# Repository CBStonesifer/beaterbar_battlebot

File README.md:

# Beater-Bar BattleBot

A 3-pound (beetleweight) combat robot designed and built across the full hardware stack: mechanical CAD, PCB layout, and embedded firmware. The goal was a **reproducible end-to-end build process** — from CAD model to fabricated board to driving firmware — rather than peak performance. V2 will optimize for weight and combat performance.

> A full reflection on the build is on Substack: [Earning Three Minutes in the Ring](https://open.substack.com/pub/carterstonesifer/p/earning-three-minutes-in-the-ring?r=2y2f28&utm_campaign=post&utm_medium=web&showWelcomeOnShare=true)

**Skills demonstrated:** Fusion 360 / FDM prototyping · KiCad schematic + layout · custom footprint creation · Gerber fabrication output · ESP32 embedded C · RC PWM decode · LEDC motor PWM · skid-steer mixing

---

## Repo Structure

```
cad/          — 3D-printable chassis, wheels, and weapon (STL + 3MF)
pcb/          — KiCad schematic, layout, custom footprints, and gerbers
firmware/     — Arduino sketch for ESP32 (RC decode + motor mixing)
```

---

## Design Decisions

- **Beater bar weapon** — a relatively simple and proven design with high impact potential in the arena. The main weakness is being flipped; a lower profile in V2 addresses this directly.
- **Unified motor driver (DRV8833)** — the same driver module is used for all three motors (left drive, right drive, weapon). Simplifies the BOM and firmware; the weapon motor runs off its own dedicated DRV8833 instance.
- **Skid-steer drivetrain** — keeps mechanical complexity low while maintaining full mobility. No steering linkage, no Ackermann geometry, just two independently driven wheels.
- **Belt-driven weapon** — the GT2 20T/60T pulley ratio amplifies the motor's output speed to spin the beater bar faster than a direct-drive setup would allow.
- **Unitary printed body** — a single-piece chassis provides structural strength without mechanical interlocks between parts. Drive and weapon geometry were validated as separate prints first, then merged once the layout was confirmed.

---

## Bill of Materials

| # | Component | Part | Qty | Specs | Link |
|---|-----------|------|-----|-------|------|
| 1 | MCU | ESP32 dev board | 1 | Dual-core 32-bit, 240 MHz, 3.3V, WiFi + BT | [Amazon](https://www.amazon.com/dp/B0C9TGJRPH) |
| 2 | Motor driver | DRV8833 | 3 | 1.5 A continuous, 2 A peak | [Amazon](https://www.amazon.com/dp/B0DXF6LZB1) |
| 3 | Buck regulator | LM2596 | 1 | 3–40V in, 1.5–35V adj out | [Amazon](https://www.amazon.com/dp/B0DBVYP91F) |
| 4 | Battery | 2S LiPo | 1 | 7.4V, 2000mAh, T-plug | [Amazon](https://www.amazon.com/dp/B0FCFVWS1K) |
| 5 | RC transmitter + receiver | — | 1 set | PWM out, 2-channel minimum | [Amazon](https://www.amazon.com/dp/B0FJDFJ38M) |
| 6 | Drive motors | 390 brushed | 2 | 6–12V, 6,300 RPM @ 12V, 1A no-load, 2.3mm shaft | [Amazon](https://www.amazon.com/dp/B01M58POHF) |
| 7 | Weapon motor | 550 brushed, 55T | 1 | 7.4V (2S), 36mm dia, 3.17mm shaft | [Amazon](https://www.amazon.com/dp/B0FXG6J3Z9) |
| 8 | Weapon belt drive | GT2 pulley + belt | 1 set | 20T / 60T, 8mm bore, 200mm belt | [Amazon](https://www.amazon.com/dp/B08QZ4365D) |
| 9 | Connectors | JST-XH 3-pin | 10 pairs | 2.54mm pitch, 26AWG, 200mm | [Amazon](https://www.amazon.com/dp/B0D3LVLMP9) |
| 10 | Print filament | PLA-CF 1.75mm | 1 spool | 1kg, carbon-fiber reinforced | [Amazon](https://www.amazon.com/dp/B0D7VV1YC7) |

---

## CAD

**Tool:** Fusion 360 → FDM (PLA-CF)  
**All parts:** `cad/` — available as both `.stl` and `.3mf`

| File | Description |
|------|-------------|
| `chassis.stl` / `.3mf` | Unitary chassis: electronics bay, drive motor mounts, weapon mount |
| `drive_wheel.stl` / `.3mf` | Drive wheels (print ×2) |
| `weapon_impactor.stl` / `.3mf` | Beater-bar weapon impactor |

Drive and weapon subsystems were first validated as separate prints, then consolidated into a single `chassis` once geometry was confirmed. Total bot target: ≤ 3 lb; drive motors are the dominant mass — body is designed to be as light as possible.

| | |
|---|---|
|  |  |
| *Fusion 360 render — `chassis`* | *Mark 1 assembled — PCB and drive motor installed* |

---

## ECAD

**Tool:** KiCad 7  
**Fabrication output:** `pcb/gerbers/battlebot_gerbers_v1.zip` — ready to send to any fab house

### Files

| File | Purpose |
|------|---------|
| `pcb/BattleBot.kicad_sch` | Full schematic |
| `pcb/BattleBot.kicad_pcb` | Board layout |
| `pcb/BattleBot-parts.kicad_sym` | Custom KiCad symbol library |
| `pcb/BattleBot.pretty/` | Custom footprint library (6 footprints) |
| `pcb/gerbers/` | Gerber + drill files |

### Power Architecture

```
LiPo ──→ LM2596 (buck) ──→ 5V ──→ ESP32-WROVER-E
LiPo ──→ DRV8833 (×3) ──→ Drive motors + weapon motor (direct VBAT)
```

### GPIO Pin Assignments

| Signal | ESP32 GPIO |
|--------|-----------|
| RC Steering (PWM in) | 35 |
| RC Throttle (PWM in) | 34 |
| RC Weapon toggle (PWM in) | 18 |
| Left motor IN1 | 25 |
| Left motor IN2 | 26 |
| Right motor IN1 | 27 |
| Right motor IN2 | 14 |
| Weapon motor IN1 | 2 |
| Weapon motor IN2 | 15 |
| UART0 debug | 115200 baud |

### Custom Footprints

All footprints in `pcb/BattleBot.pretty/` were drawn from datasheets:

| Footprint | File |
|-----------|------|
| ESP32-WROVER-E | `ESP32-WROVER-E.kicad_mod` |
| DRV8833 | `DRV8833.kicad_mod` |
| LM2596 | `LM2596.kicad_mod` |
| RC Receiver | `Receiver.kicad_mod` |
| 3-pin connector | `3Pin-Connector.kicad_mod` |
| Test point pad | `Testpoint-Pad.kicad_mod` |

*Schematic — `BattleBot.kicad_sch`*

| | |
|---|---|
|  |  |
| *Layout — `BattleBot.kicad_pcb`* | *KiCad 3D render* |

*Fabricated and populated board*

---

## Firmware

**Toolchain:** Arduino IDE + ESP32 board support package  
**Board target:** ESP32 Wrover Module  
**Sketch:** `firmware/signal_driver/signal_driver.ino`

### Control Loop

```
loop()
  ├── pulseIn GPIO 35/34/18  — read steering, throttle, weapon (25ms timeout each)
  ├── failsafe check         — any invalid/missing pulse → stopAll() and skip frame
  ├── steeringFromPulse()    — map to [-100, 100] → deadband
  ├── throttleFromPulse()    — map to [-100, 100] → deadband
  ├── mixAndDrive()          — skid-steer mix → setMotor() → LEDC PWM duty
  └── setWeapon()            — full speed on WEAPON_IN1 when pulse > 1500 µs
```

> **Failsafe:** `pulseIn` returns 0 on timeout, and a valid RC frame sits ~1000–2000 µs. Any pulse outside the 900–2100 µs band is treated as link loss — all drive and weapon output is cut for that loop. Without this guard a lost signal maps to full reverse, so the bot drives off on its own when the transmitter drops.

### Motor Mixing

- **Straight:** `left = right = throttle`
- **Driving turn:** inner wheel = `throttle × (TURN_MIX_RATIO / 100)`
- **Spin-in-place:** `left = +steering`, `right = −steering`

### Calibration Constants

| Constant | V1 Value | Purpose |
|----------|----------|---------|
| `STEERING_MIN` | 965 µs | Min receiver pulse |
| `STEERING_MAX` | 1882 µs | Max receiver pulse |
| `THROTTLE_MIN` | 1055 µs | Min throttle pulse |
| `THROTTLE_IDLE` | 1565 µs | Neutral position |
| `THROTTLE_MAX` | 2000 µs | Max throttle pulse |
| `DEADBAND` | 5 | Noise rejection around neutral |
| `TURN_MIX_RATIO` | 50 | Inner-wheel scaling (0–100) |
| `PWM_FREQ` | 20,000 Hz | LEDC motor PWM frequency |
| `PWM_RES` | 8-bit | Duty cycle range (0–255) |

> These constants are radio-specific. Re-measure pulse widths for your transmitter before first drive.

### Flash Instructions

1. Install ESP32 board support in Arduino IDE
2. Open `firmware/signal_driver/signal_driver.ino`
3. Select **ESP32 Wrover Module**, set the correct COM port
4. Update calibration constants for your RC radio
5. Upload

---

## Testing & Validation

The bot was driven under full battery power with all systems operating independently:

- **Drive** — successfully accelerated, turned, and reversed at varying speeds under RC control.
- **Weapon** — spun up to full speed and was toggled on and off from the transmitter.
- **Carpet performance** — struggled on carpet. The wheels lacked grip, and the design relies on the body sliding along the ground to stay low against opponents — which doesn't work well on high-friction surfaces.
- **Battery connector** — the 3-pin plugs do not physically prevent reverse polarity insertion. Connecting the battery backwards is easy to do and will damage the board.

<br><em>ESP32 after a flipping power contacts</em>

---

## Known Issues & Further Improvements (V2)

- **Chassis Side Overhangs** — the overhangs on the side were quickly added to thicken the width of the walls to strengthen the bot, and for style. They provide a grip for another bot to easily flip the vehicle. The next design should minimize the gap between the side edges and the ground.
- **Hard Power Cut-Off** — as per NHRL rules, the bot requires a quick physical power disconnect to disable movement and weapon systems, not just a code deactivation.
- **Reverse-polarity protection** — V1 fried a board because the 3-pin power plug can be inserted backwards. V2 should add a series Schottky / P-channel MOSFET ideal-diode at the battery input *and* a keyed/slotted connector so the battery physically can't seat the wrong way. The board itself is cheap and easily reproducible from the gerbers, so losing one to this wasn't costly — but it's a trivial thing to design out.
- **Undersized motor drivers** — the DRV8833 is rated 1.5 A continuous / 2 A peak, but the 390 drive motors stall around 5–7 A and the 550 weapon motor well above that. Under real load the part is pushed past its peak, where it current-limits or fails. V2 should size the H-bridge to *stall* current, not no-load current, and add a firmware soft-start ramp so the weapon spins up gradually instead of slamming to full duty and drawing a large inrush spike. The broader lesson: parts that work together aren't necessarily matched on performance — each one needs headroom for the worst case the system will actually see.
- **Hardened weapon impactor** — machine or print in PETG/nylon/polycarbonate; evaluate a metal impactor for the beater bar.
- **Weight optimization** — the current design is 2.76 lbs, which leaves room to upgrade/add additional parts (i.e. the weapon material should be metal).
- **Optimize print settings** — a final print with more granular layer heights and higher infill will strengthen the hull.
- **A Roof** — the top of the bot needs a solid roof that could also act as a battery retainer. Batteries are currently loose within the chassis.
- **Sweet Paint Job** — the bot needs some decals and a layer of spray paint to make it look more threatening.
- **Wheel Grips and Covers** — the wheels are exposed and use electrical tape for grip. They must be better protected, as immobility is an immediate loss in the arena. A set of proper tires would help with mobility, and the front shovel can catch on uneven surfaces.
- **Beater Bar orientation is reversed** — the edge of the beater bar faces inward, counter to the direction the bar spins. Opposing robots are hit with the blunt edge of the weapon rather than the sharp, scraping side that should brush close to the ground.
- **Blocking RC read (`pulseIn`)** — the firmware reads each RC channel sequentially using `pulseIn()`, which blocks for up to ~25ms per channel, so a full loop can take ~75ms. Signal loss is now handled (an invalid/missing pulse disarms all motors), but the read is still blocking. V2 should use hardware interrupts or RTOS tasks to read channels concurrently.

---

## Tools Required

- **3D printer** — Bambu A1 (or equivalent FDM printer capable of PLA-CF)
- **Soldering iron** — flux is mandatory; makes the joints significantly cleaner and easier
- **Wire stripper**
- **Extra header pins**
- **Assorted screws and a screwdriver**

---

## Status

| Version | Status | Focus |
|---------|--------|-------|
| V1 | Complete | Cost-optimized, full-stack process established |
| V2 | Planned | Weight/performance, hardened materials, active fault handling |

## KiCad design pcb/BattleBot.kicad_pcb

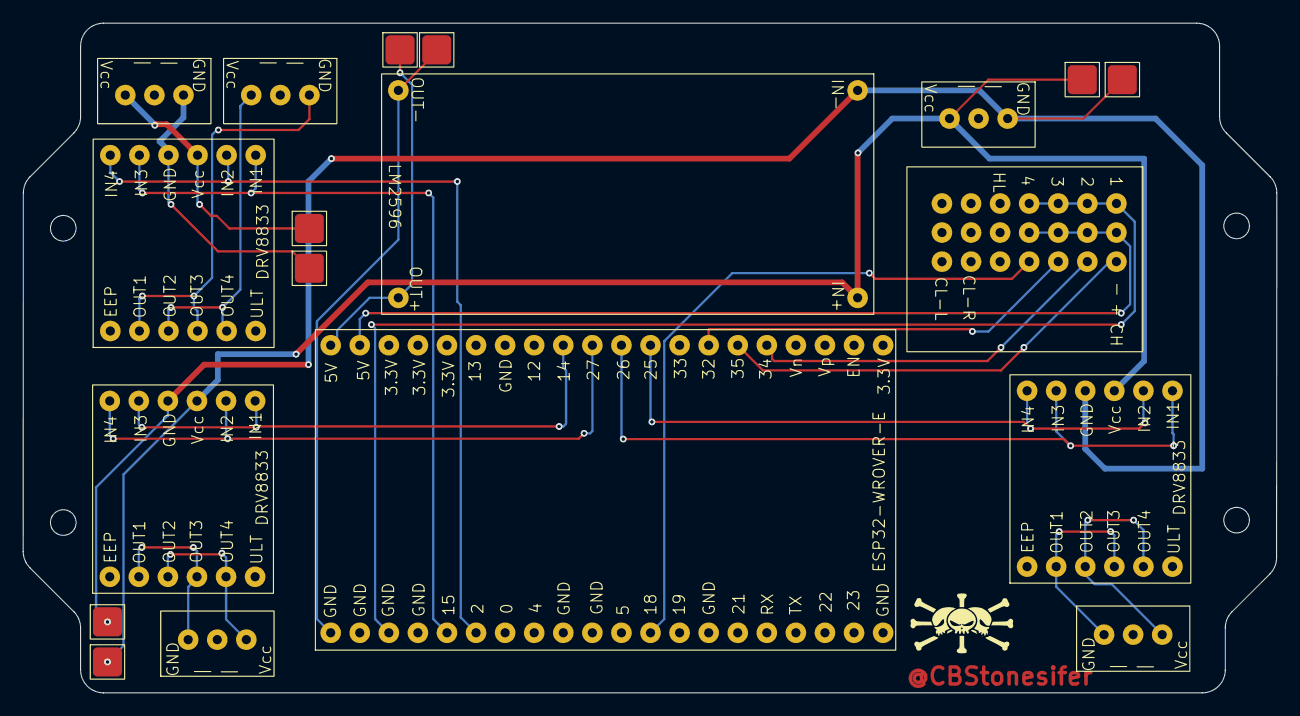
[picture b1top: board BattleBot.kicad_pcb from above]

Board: 4 copper layers, 109.5 x 58.5 mm, 19 parts (0 on the bottom side), 24 nets.

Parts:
B1: 3Pin-Connector
B2: Vcc; 3Pin-Connector
Buck1: LM2596
J1: WeaponMotor; 3Pin-Connector
J2: Motor1; 3Pin-Connector
J3: Motor2; 3Pin-Connector
MD_TP1, MD_TP2, MD_TP3, MD_TP4, MD_TP5, MD_TP6, MD_TP7, MD_TP8: Motor Driver Test Point 1; Testpoint-Pad
MicroController1: ESP32-WROVER-E
MotorDriver1, MotorDriver2: DRV8833
Receiver1: Receiver
WeaponDriver1: DRV8833

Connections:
unnamed: B1.3 (GND), MD_TP7.1 (1_1), WeaponDriver1.9 (GND)
unnamed: B1.1 (Vcc), MD_TP8.1 (1_1), WeaponDriver1.10 (VCC)
unnamed: B2.3 (GND), Buck1.2 (IN-), MD_TP2.1 (1_1), MD_TP3.1 (1_1), MotorDriver1.9 (GND), MotorDriver2.9 (GND)
unnamed: B2.1 (Vcc), Buck1.1 (IN+), MD_TP1.1 (1_1), MD_TP4.1 (1_1), MotorDriver1.10 (VCC), MotorDriver2.10 (VCC)
unnamed: Buck1.3 (OUT+), MD_TP5.1 (1_1), MicroController1.20 (5V)
unnamed: Buck1.4 (OUT-), MD_TP6.1 (1_1), MicroController1.21 (GND)
unnamed: J1.1, WeaponDriver1.3 (OUT2), WeaponDriver1.5 (OUT4)
unnamed: J1.3, WeaponDriver1.2 (OUT1), WeaponDriver1.4 (OUT3)
unnamed: J2.1, MotorDriver1.3 (OUT2), MotorDriver1.5 (OUT4)
unnamed: J2.3, MotorDriver1.2 (OUT1), MotorDriver1.4 (OUT3)
unnamed: J3.1, MotorDriver2.3 (OUT2), MotorDriver2.5 (OUT4)
unnamed: J3.3, MotorDriver2.2 (OUT1), MotorDriver2.4 (OUT3)
unnamed: MicroController1.26 (GPIO2), WeaponDriver1.7 (IN4), WeaponDriver1.11 (IN2)
unnamed: MicroController1.12 (GPIO14), MotorDriver1.8 (IN3), MotorDriver1.12 (IN1)
unnamed: MicroController1.25 (GPIO15), WeaponDriver1.8 (IN3), WeaponDriver1.12 (IN1)
unnamed: MicroController1.32 (GPIO18), Receiver1.12 (SIG_4)
unnamed: MicroController1.9 (GPIO25), MotorDriver2.7 (IN4), MotorDriver2.11 (IN2)
unnamed: MicroController1.10 (GPIO26), MotorDriver2.8 (IN3), MotorDriver2.12 (IN1)
unnamed: MicroController1.11 (GPIO27), MotorDriver1.7 (IN4), MotorDriver1.11 (IN2)
unnamed: MicroController1.7 (GPIO32), Receiver1.9 (SIG_3)
unnamed: MicroController1.5 (GPIO34), Receiver1.6 (SIG_2)
unnamed: MicroController1.6 (GPIO35), Receiver1.3 (SIG_1)
unnamed: MicroController1.23 (GND), Receiver1.1 (GND_1), Receiver1.4 (GND_2), Receiver1.7 (GND_3), Receiver1.10 (GND_4)
unnamed: MicroController1.19 (5V), Receiver1.2 (VCC_1), Receiver1.5 (VCC_2), Receiver1.8 (VCC_3), Receiver1.11 (VCC_4)

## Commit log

2026-06-11 clean up files
2026-06-18 mark 1
2026-06-27 documentation
2026-06-27 image insert
2026-06-27 polish
2026-06-29 substack link
